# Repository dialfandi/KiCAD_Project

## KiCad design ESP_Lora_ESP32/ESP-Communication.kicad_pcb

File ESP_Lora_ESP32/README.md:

# **ESP-32-LoRa PCB Design Prototype**

## Design using KiCAD Software V6.0

### The Design is my private project, i'am created it to learn and reverse my project last year with a same system hardware

# Spesification
1. Supply 3 - 36 V 3A
2. ESP32-S3
3. Lora Communication
4. RS485 Communication
5. Serial Communication

## Noted : This design has never been printed and tested

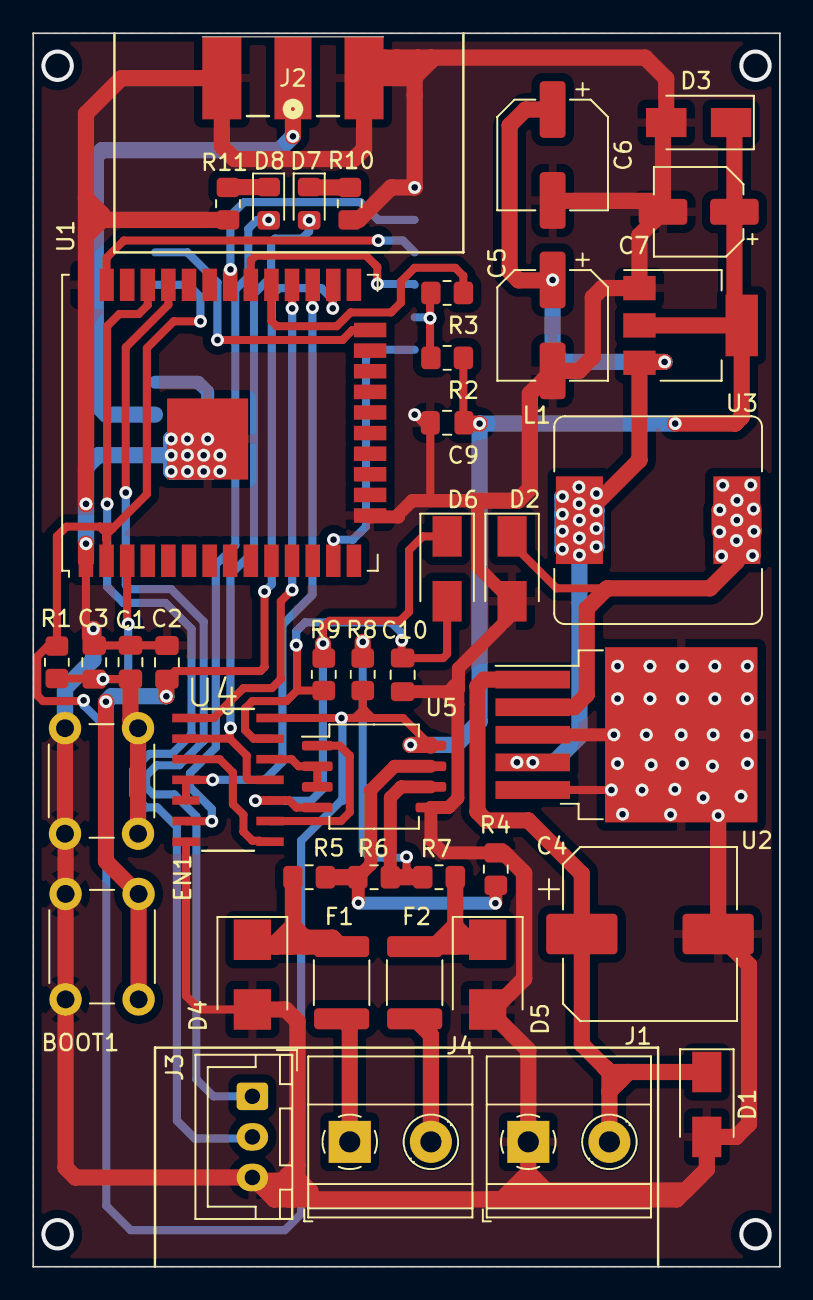
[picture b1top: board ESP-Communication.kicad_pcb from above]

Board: 2 copper layers, 46.0 x 76.0 mm, 43 parts (1 on the bottom side), 34 nets.

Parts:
BOOT1: SW_Push; SW_PUSH_6mm
C1, C2, C3: 0.1uF; C_0805_2012Metric_Pad1.18x1.45mm_HandSolder
C4: 330uF; CP_Elec_10x10.5
C5: 220uF; CP_Elec_6.3x9.9
C6: 110uF; CP_Elec_6.3x9.9
C7: 47uF; CP_Elec_5x5.4
C9: 0,1uF; C_0805_2012Metric_Pad1.18x1.45mm_HandSolder
C10: 33Pf; C_0805_2012Metric_Pad1.18x1.45mm_HandSolder
D1, D2, D3: SS34; D_SMA
D4, D5: DTVS; D_SMB
D6: SS14; D_SMA
D7, D8: LED; LED_0805_2012Metric_Pad1.15x1.40mm_HandSolder
EN1: SW_Push; SW_PUSH_6mm
F1, F2: Polyfuse; Fuse_1812_4532Metric_Pad1.30x3.40mm_HandSolder
J1, J4: PTR; TerminalBlock_Phoenix_MKDS-1,5-2_1x02_P5.00mm_Horizontal
J2: CON-ANTENA; CONN_ANTENA_SMA_CIN
J3: UART-DOWNLOAD; JST_XH_B3B-XH-A_1x03_P2.50mm_Vertical
L1: 33uH; L_Bourns_SRR1260
MOD1: RFM98W-433S2; XCVR_RFM98W-433S2
R1, R2, R3: 10K; R_0805_2012Metric_Pad1.20x1.40mm_HandSolder
R4, R8: 560; R_0805_2012Metric_Pad1.20x1.40mm_HandSolder
R5, R7: 0; R_0805_2012Metric_Pad1.20x1.40mm_HandSolder
R6: 120; R_0805_2012Metric_Pad1.20x1.40mm_HandSolder
R9: 56K; R_0805_2012Metric_Pad1.20x1.40mm_HandSolder
R10, R11: 470; R_0805_2012Metric_Pad1.20x1.40mm_HandSolder
U1: ESP32-WROOM-32U
U2: LM2596S-5; TO-263-5_TabPin3
U3: AMS1117-3.3; SOT-223-3_TabPin2
U4: 74HC04D; SOIC127-704xx
U5: MAX485E; SO-8_5.3x6.2mm_P1.27mm

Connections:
+3V3: C7.1, C9.1, D3.1 (K), MOD1.13 (3.3V), R1.1, R2.1, R8.1, U1.2 (VDD), U3.2 (VO), U4.14 (VCC), U5.8 (VCC)
+5V: C5.1, C6.1, L1.2, U2.4 (FB), U3.3 (VI)
/1Y-NOTIF: D7.2 (A), U4.2 (1Y), U4.11 (5A)
/2A-4Y: U4.3 (2A), U4.8 (4Y)
/3Y-NOTIF: D8.2 (A), U4.6 (3Y)
/6A-MOD: C10.2, D6.2 (A), R9.1, U4.13 (6A)
/BOOT: BOOT1.2, C2.2, U1.26 (IO4)
/D0-LORA: MOD1.14 (DIO0), U1.24 (IO2)
/DE/RE: U4.12 (6Y), U5.2 (~RE), U5.3 (DE)
/DI: D6.1 (K), R9.2, U4.10 (5Y), U5.4 (DI)
/EN: C1.2, C3.2, EN1.2, R1.2, U1.3 (EN)
/MISO-LORA: MOD1.2 (MISO), U1.31 (IO19)
/MOSI-LORA: MOD1.3 (MOSI), U1.37 (IO23)
/NSS-IO5: R3.2, U1.29 (IO5)
/NSS-LORA: MOD1.5 (NSS), R2.2, R3.1
/RO: U4.9 (4A), U5.1 (RO)
/RST-LORA: MOD1.6 (RESET), U1.13 (IO14)
/RX0: J3.1, U1.34 (RXD0/IO3)
/RX-MOD: U1.27 (IO16), U4.4 (2Y), U4.5 (3A)
/SCK-LORA: MOD1.4 (SCK), U1.30 (IO18)
/TX0: J3.2, U1.35 (TXD0/IO1)
/TX-MOD: U1.28 (IO17), U4.1 (1A)
GND: BOOT1.1, C1.1, C2.1, C3.1, C4.2, C5.2, C6.2, C7.2, C9.2, C10.1, D1.2 (A), D2.2 (A), D3.2 (A), D4.2 (A2), D5.2 (A2), EN1.1, J1.1, J2.2, J2.3, J2.4, J2.5, J3.3, MOD1.1 (GND), MOD1.8 (GND__2), MOD1.10 (GND__4), R4.2, R10.2, R11.2, U1.1 (GND), U1.15 (GND), U1.38 (GND), U1.39 (GND), U2.3 (GND), U2.5 (~ON/OFF), U3.1 (GND), U4.7 (GND), U5.5 (GND)
unnamed: C4.1, D1.1 (K), J1.2, U2.1 (VIN)
unnamed: D2.1 (K), L1.1, U2.2 (OUT)
unnamed: D4.1 (A1), F1.1, R5.1
unnamed: D5.1 (A1), F2.1, R7.1
unnamed: D7.1 (K), R10.1
unnamed: D8.1 (K), R11.1
unnamed: F1.2, J4.1
unnamed: F2.2, J4.2
unnamed: J2.1, MOD1.9 (ANT)
unnamed: R4.1, R5.2, R6.2, U5.7 (B)
unnamed: R6.1, R7.2, R8.2, U5.6 (A)

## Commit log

2024-09-18 Create Folder
2024-09-18 Inital Commit
2024-09-18 Remove file or folder
2024-09-18 remove add file
2024-09-18 Add .gitkeep to track folder
2024-09-18 Add Readme.md in Folder
